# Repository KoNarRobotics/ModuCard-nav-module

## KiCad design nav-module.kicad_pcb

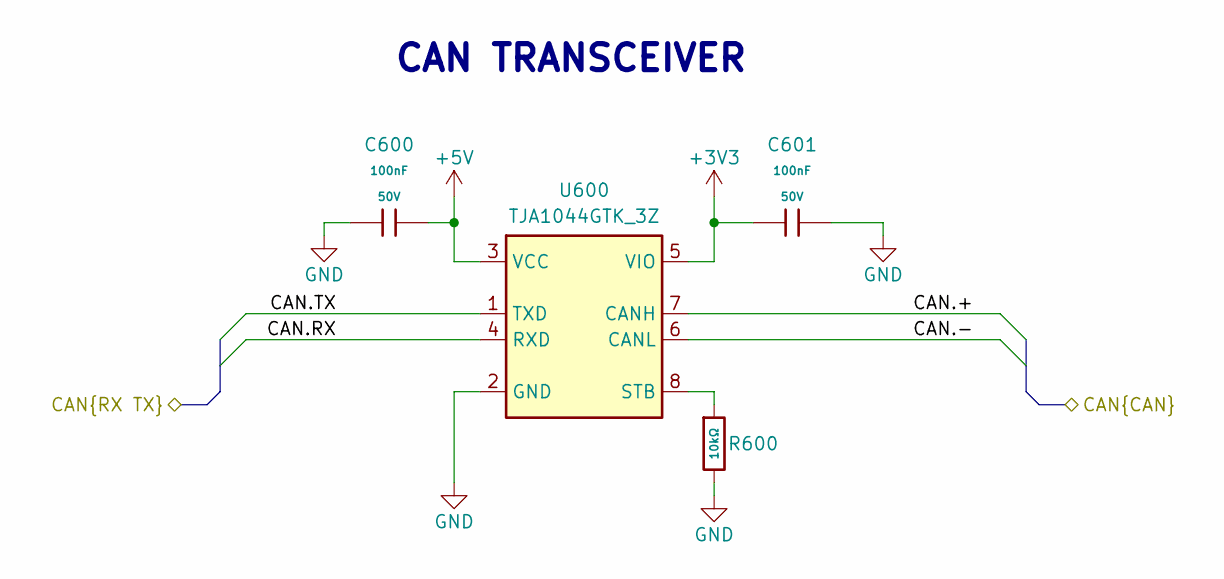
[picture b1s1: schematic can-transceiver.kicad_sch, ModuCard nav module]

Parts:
C600, C601: 100nF; C_0402; Voltage Rated 50V; Tolerance ±10%; Part CL05B104KB54PNC; LCSC C307331
R600: 10kΩ; R_0402; Overload Voltage (Max) 50V; Tolerance ±1%; Part 0402WGF1002TCE; LCSC C25744
U600: TJA1044GTK_3Z; HVSON-8-1EP_3x3mm_P0.65mm_EP1.6x2.4mm; Manufacturer_Part_Number TJA1044GTK/3Z

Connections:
+3V3: C601.1, U600.5 (VIO); also elsewhere on the board
+5V: C600.2, U600.3 (VCC); also elsewhere on the board
/Backplane/CAN2.+: U600.7 (CANH); also elsewhere on the board
/Backplane/CAN2.-: U600.6 (CANL); also elsewhere on the board
/CAN transceiver 2/CAN.RX: U600.4 (RXD); also elsewhere on the board
/CAN transceiver 2/CAN.TX: U600.1 (TXD); also elsewhere on the board
GND: C600.1, C601.2, R600.2, U600.2 (GND), U600.9 (EP); also elsewhere on the board
unnamed: R600.1, U600.8 (STB)

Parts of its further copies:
C500, C501: 100nF; C_0402; Voltage Rated 50V; Tolerance ±10%; Part CL05B104KB54PNC; LCSC C307331
R500: 10kΩ; R_0402; Overload Voltage (Max) 50V; Tolerance ±1%; Part 0402WGF1002TCE; LCSC C25744
U500: TJA1044GTK_3Z; HVSON-8-1EP_3x3mm_P0.65mm_EP1.6x2.4mm; Manufacturer_Part_Number TJA1044GTK/3Z

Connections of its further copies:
+3V3: C501.1, U500.5 (VIO); also elsewhere on the board
+5V: C500.2, U500.3 (VCC); also elsewhere on the board
/Backplane/CAN1.+: U500.7 (CANH); also elsewhere on the board
/Backplane/CAN1.-: U500.6 (CANL); also elsewhere on the board
/CAN transceiver 1/CAN.RX: U500.4 (RXD); also elsewhere on the board
/CAN transceiver 1/CAN.TX: U500.1 (TXD); also elsewhere on the board
GND: C500.1, C501.2, R500.2, U500.2 (GND), U500.9 (EP); also elsewhere on the board
unnamed: R500.1, U500.8 (STB)

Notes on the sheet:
CAN TRANSCEIVER

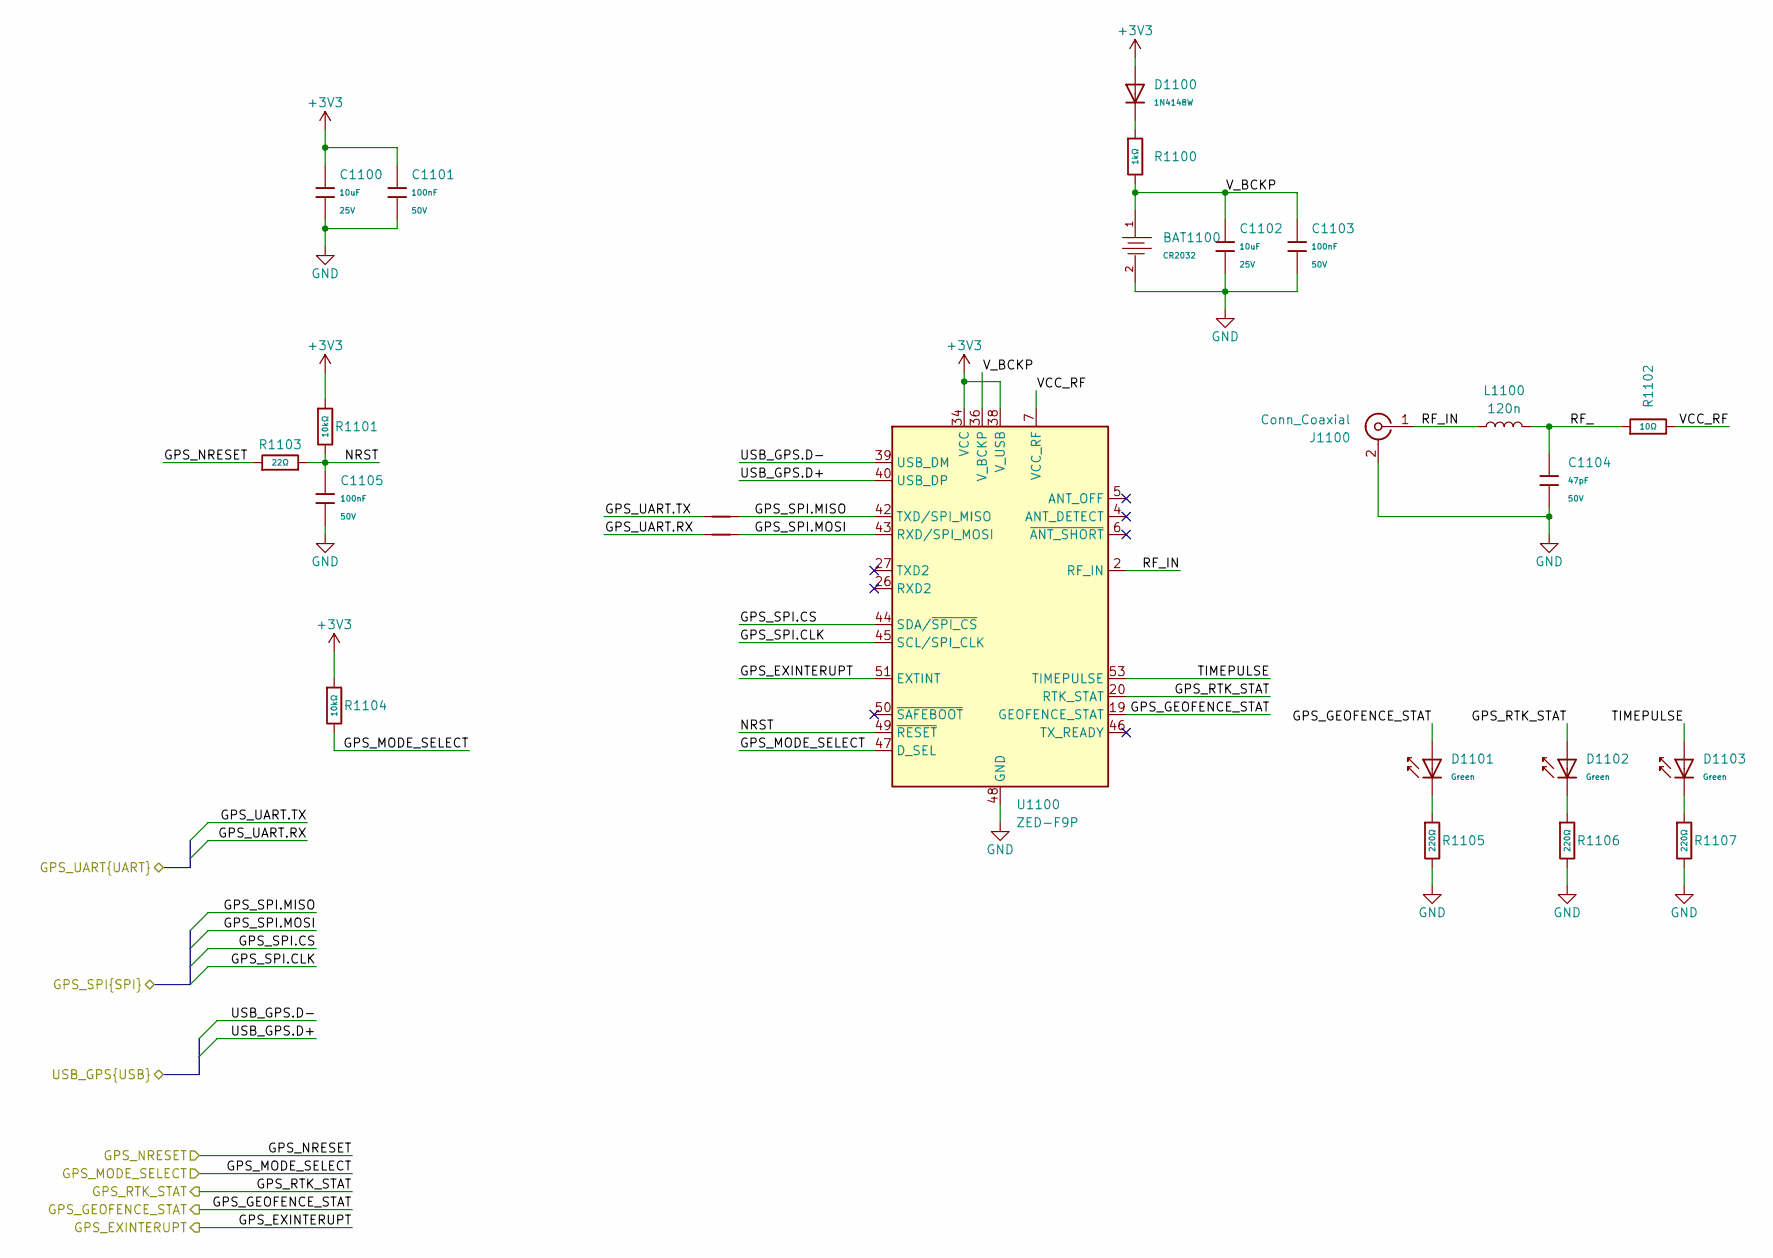
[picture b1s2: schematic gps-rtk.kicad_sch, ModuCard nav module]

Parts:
BAT1100: CR2032; BatteryHolder_Keystone_1060_1x2032; Part BS-07-A1BJ001; LCSC C2979167
C1100, C1102: 10uF; C_0603; Voltage Rated 25V; Tolerance ±20%; Part CL10A106MA8NRNC; LCSC C96446
C1101, C1103, C1105: 100nF; C_0402; Voltage Rated 50V; Tolerance ±10%; Part CL05B104KB54PNC; LCSC C307331
C1104: 47pF; C_0402; Voltage Rated 50V; Tolerance ±5%; Part 0402CG470J500NT; LCSC C1567
D1100: 1N4148W; D_SOD-123; Forward Voltage (Vf@If) 1V@50mA; Reverse Voltage (Vr) 75V; Part 1N4148W; LCSC C81598
D1101, D1102, D1103: Green; D_0603; Part 19-217/GHC-YR1S2/6T; LCSC C2986059
J1100: Conn_Coaxial; SMA_Amphenol_901-143_Horizontal
L1100: 120n; L_0402_1005Metric
NT1100, NT1101: NetTie_2; NetTie-2_SMD_Pad0.5mm
R1100: 1kΩ; R_0402; Overload Voltage (Max) 50V; Tolerance ±1%; Part 0402WGF1001TCE; LCSC C11702
R1101, R1104: 10kΩ; R_0402; Overload Voltage (Max) 50V; Tolerance ±1%; Part 0402WGF1002TCE; LCSC C25744
R1102: 10Ω; R_0402; Overload Voltage (Max) 50V; Tolerance ±1%; Part 0402WGF100JTCE; LCSC C25077
R1103: 22Ω; R_0402; Overload Voltage (Max) 50V; Tolerance ±1%; Part 0402WGF220JTCE; LCSC C25092
R1105, R1106, R1107: 220Ω; R_0402; Overload Voltage (Max) 50V; Tolerance ±1%; Part 0402WGF2200TCE; LCSC C25091
U1100: ZED-F9P; ublox_ZED

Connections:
+3V3: C1100.1, C1101.1, D1100.2, R1101.1, R1104.1, U1100.33 (VCC), U1100.34 (VCC), U1100.38 (V_USB); also elsewhere on the board
/GPS-RTK/GPS_EXINTERUPT: U1100.51 (EXTINT); also elsewhere on the board
/GPS-RTK/GPS_GEOFENCE_STAT: D1101.2, U1100.19 (GEOFENCE_STAT); also elsewhere on the board
/GPS-RTK/GPS_MODE_SELECT: R1104.2, U1100.47 (D_SEL); also elsewhere on the board
/GPS-RTK/GPS_NRESET: R1103.1; also elsewhere on the board
/GPS-RTK/GPS_RTK_STAT: D1102.2, U1100.20 (RTK_STAT); also elsewhere on the board
/GPS-RTK/GPS_SPI.CLK: U1100.45 (SCL/SPI_CLK); also elsewhere on the board
/GPS-RTK/GPS_SPI.CS: U1100.44 (SDA/~SPI_CS); also elsewhere on the board
/GPS-RTK/GPS_SPI.MISO: NT1100.2, U1100.42 (TXD/SPI_MISO); also elsewhere on the board
/GPS-RTK/GPS_SPI.MOSI: NT1101.2, U1100.43 (RXD/SPI_MOSI); also elsewhere on the board
/GPS-RTK/GPS_UART.RX: NT1101.1; also elsewhere on the board
/GPS-RTK/GPS_UART.TX: NT1100.1; also elsewhere on the board
/GPS-RTK/NRST: C1105.1, R1101.2, R1103.2, U1100.49 (~RESET)
/GPS-RTK/RF_: C1104.2, L1100.2, R1102.1
/GPS-RTK/RF_IN: J1100.1 (In), L1100.1, U1100.2 (RF_IN)
/GPS-RTK/TIMEPULSE: D1103.2, U1100.53 (TIMEPULSE)
/GPS-RTK/USB_GPS.D+: U1100.40 (USB_DP); also elsewhere on the board
/GPS-RTK/USB_GPS.D-: U1100.39 (USB_DM); also elsewhere on the board
/GPS-RTK/VCC_RF: R1102.2, U1100.7 (VCC_RF)
/GPS-RTK/V_BCKP: BAT1100.1, C1102.1, C1103.1, R1100.2, U1100.36 (V_BCKP)
GND: BAT1100.2, C1100.2, C1101.2, C1102.2, C1103.2, C1104.1, C1105.2, J1100.2 (Ext), R1105.2, R1106.2, R1107.2, U1100.1 (GND), U1100.3 (GND), U1100.12 (GND), U1100.14 (GND), U1100.32 (GND), U1100.37 (GND), U1100.41 (GND), U1100.48 (GND), U1100.55 (GND); also elsewhere on the board
unnamed: D1100.1, R1100.1
unnamed: D1101.1, R1105.1
unnamed: D1102.1, R1106.1
unnamed: D1103.1, R1107.1

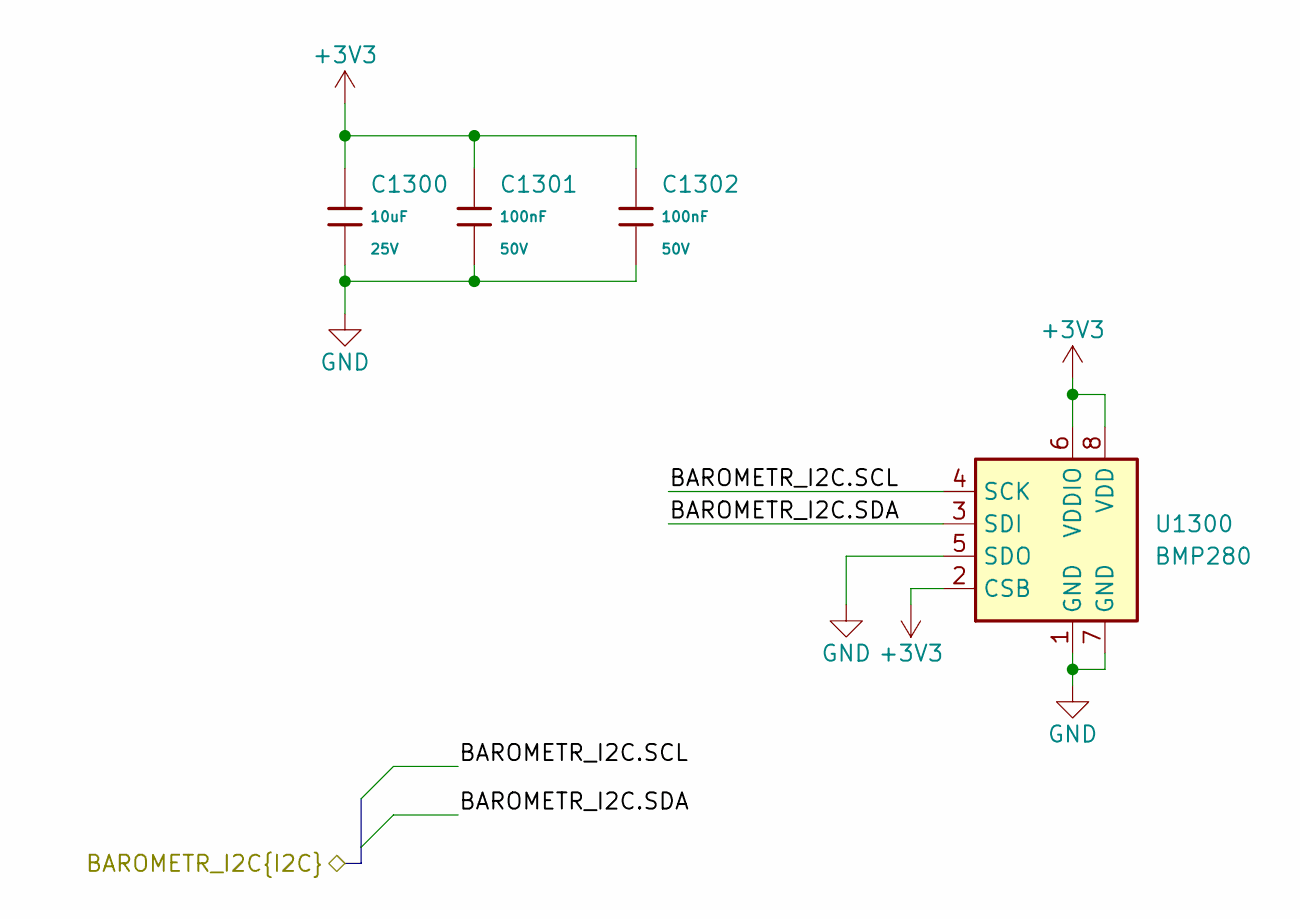
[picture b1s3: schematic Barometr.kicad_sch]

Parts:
C1300: 10uF; C_0603; Voltage Rated 25V; Tolerance ±20%; Part CL10A106MA8NRNC; LCSC C96446
C1301, C1302: 100nF; C_0402; Voltage Rated 50V; Tolerance ±10%; Part CL05B104KB54PNC; LCSC C307331
U1300: BMP280; Bosch_LGA-8_2x2.5mm_P0.65mm_ClockwisePinNumbering

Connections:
+3V3: C1300.1, C1301.1, C1302.1, U1300.2 (CSB), U1300.6 (VDDIO), U1300.8 (VDD); also elsewhere on the board
/Barometr/BAROMETR_I2C.SCL: U1300.4 (SCK); also elsewhere on the board
/Barometr/BAROMETR_I2C.SDA: U1300.3 (SDI); also elsewhere on the board
GND: C1300.2, C1301.2, C1302.2, U1300.1 (GND), U1300.5 (SDO), U1300.7 (GND); also elsewhere on the board

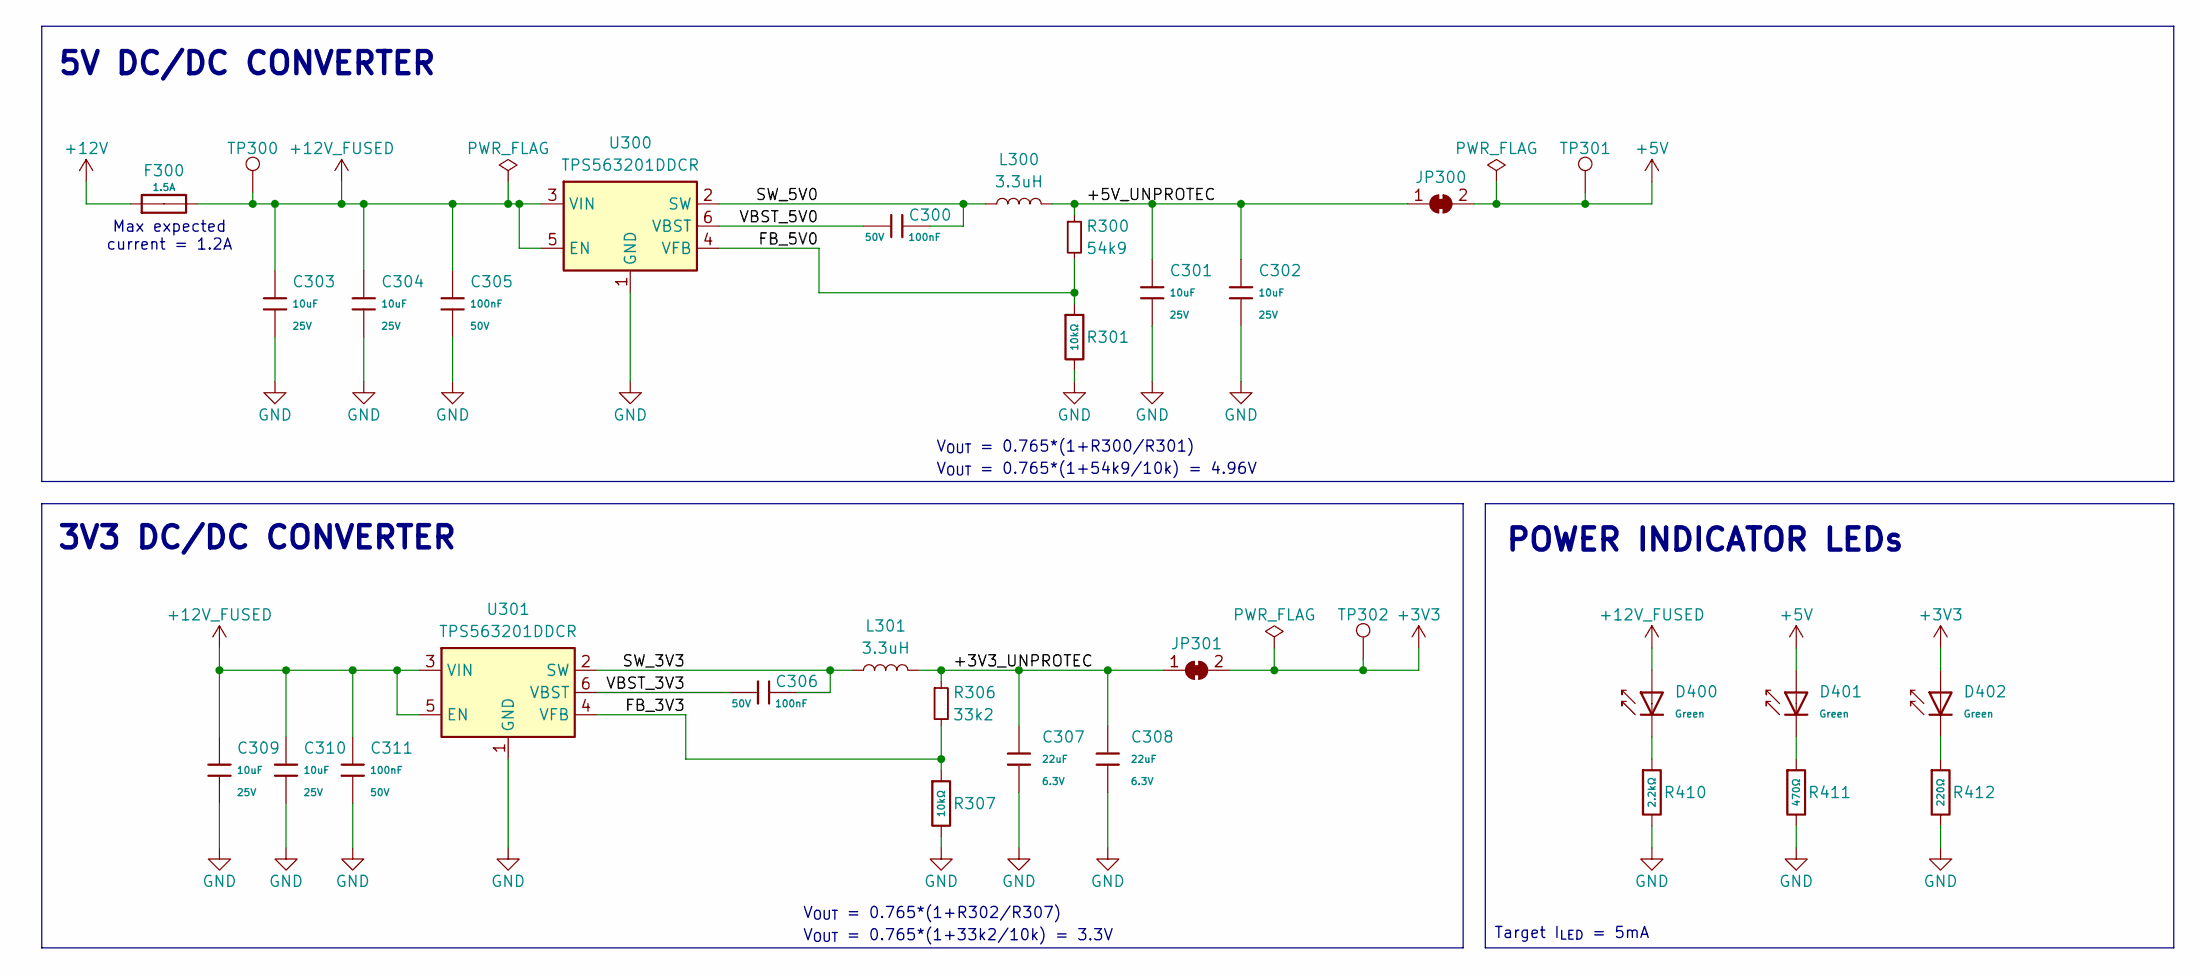
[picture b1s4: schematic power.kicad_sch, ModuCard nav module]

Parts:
C300, C305, C306, C311: 100nF; C_0402; Voltage Rated 50V; Tolerance ±10%; Part CL05B104KB54PNC; LCSC C307331
C301, C302, C303, C304, C309, C310: 10uF; C_0603; Voltage Rated 25V; Tolerance ±20%; Part CL10A106MA8NRNC; LCSC C96446
C307, C308: 22uF; C_0603; Voltage Rated 6.3V; Tolerance ±20%; Part CL10A226MQ8NRNC; LCSC C59461
D400, D401, D402: Green; D_0603; Part 19-217/GHC-YR1S2/6T; LCSC C2986059
F300: 1.5A; F_0603; Part F06F1.5; LCSC C2924957
JP300, JP301: Test Buck Vout; SolderJumper-2_P1.3mm_Open_TrianglePad1.0x1.5mm
L300, L301: 3.3uH; L_Changjiang_FXL0420
R300: 54k9; R_0402
R301, R307: 10kΩ; R_0402; Overload Voltage (Max) 50V; Tolerance ±1%; Part 0402WGF1002TCE; LCSC C25744
R306: 33k2; R_0402
R410: 2.2kΩ; R_0402; Overload Voltage (Max) 50V; Tolerance ±1%; Part 0402WGF2201TCE; LCSC C25879
R411: 470Ω; R_0402; Overload Voltage (Max) 50V; Tolerance ±1%; Part 0402WGF4700TCE; LCSC C25117
R412: 220Ω; R_0402; Overload Voltage (Max) 50V; Tolerance ±1%; Part 0402WGF2200TCE; LCSC C25091
TP300, TP301, TP302: TestPoint; TestPoint_Pad_D1.0mm
U300, U301: TPS563201DDCR; SOT-23-6

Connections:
+3V3: D402.2, JP301.2 (B), TP302.1; also elsewhere on the board
+5V: D401.2, JP300.2 (B), TP301.1; also elsewhere on the board
+12V: F300.1; also elsewhere on the board
+12V_FUSED: C303.1, C304.1, C305.2, C309.1, C310.1, C311.2, D400.2, F300.2, TP300.1, U300.3 (VIN), U300.5 (EN), U301.3 (VIN), U301.5 (EN)
/Power/+3V3_UNPROTEC: C307.1, C308.1, JP301.1 (A), L301.2, R306.1
/Power/+5V_UNPROTEC: C301.1, C302.1, JP300.1 (A), L300.2, R300.1
/Power/FB_3V3: R306.2, R307.1, U301.4 (VFB)
/Power/FB_5V0: R300.2, R301.1, U300.4 (VFB)
/Power/SW_3V3: C306.2, L301.1, U301.2 (SW)
/Power/SW_5V0: C300.2, L300.1, U300.2 (SW)
/Power/VBST_3V3: C306.1, U301.6 (VBST)
/Power/VBST_5V0: C300.1, U300.6 (VBST)
GND: C301.2, C302.2, C303.2, C304.2, C305.1, C307.2, C308.2, C309.2, C310.2, C311.1, R301.2, R307.2, R410.2, R411.2, R412.2, U300.1 (GND), U301.1 (GND); also elsewhere on the board
unnamed: D400.1, R410.1
unnamed: D401.1, R411.1
unnamed: D402.1, R412.1

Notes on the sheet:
V_{OUT} = 0.765*(1+33k2/10k) = 3.3V
Max expected current = 1.2A
V_{OUT} = 0.765*(1+R302/R307)
Target I_{LED} = 5mA
V_{OUT} = 0.765*(1+R300/R301)
5V DC/DC CONVERTER
V_{OUT} = 0.765*(1+54k9/10k) = 4.96V
POWER INDICATOR LEDs
3V3 DC/DC CONVERTER

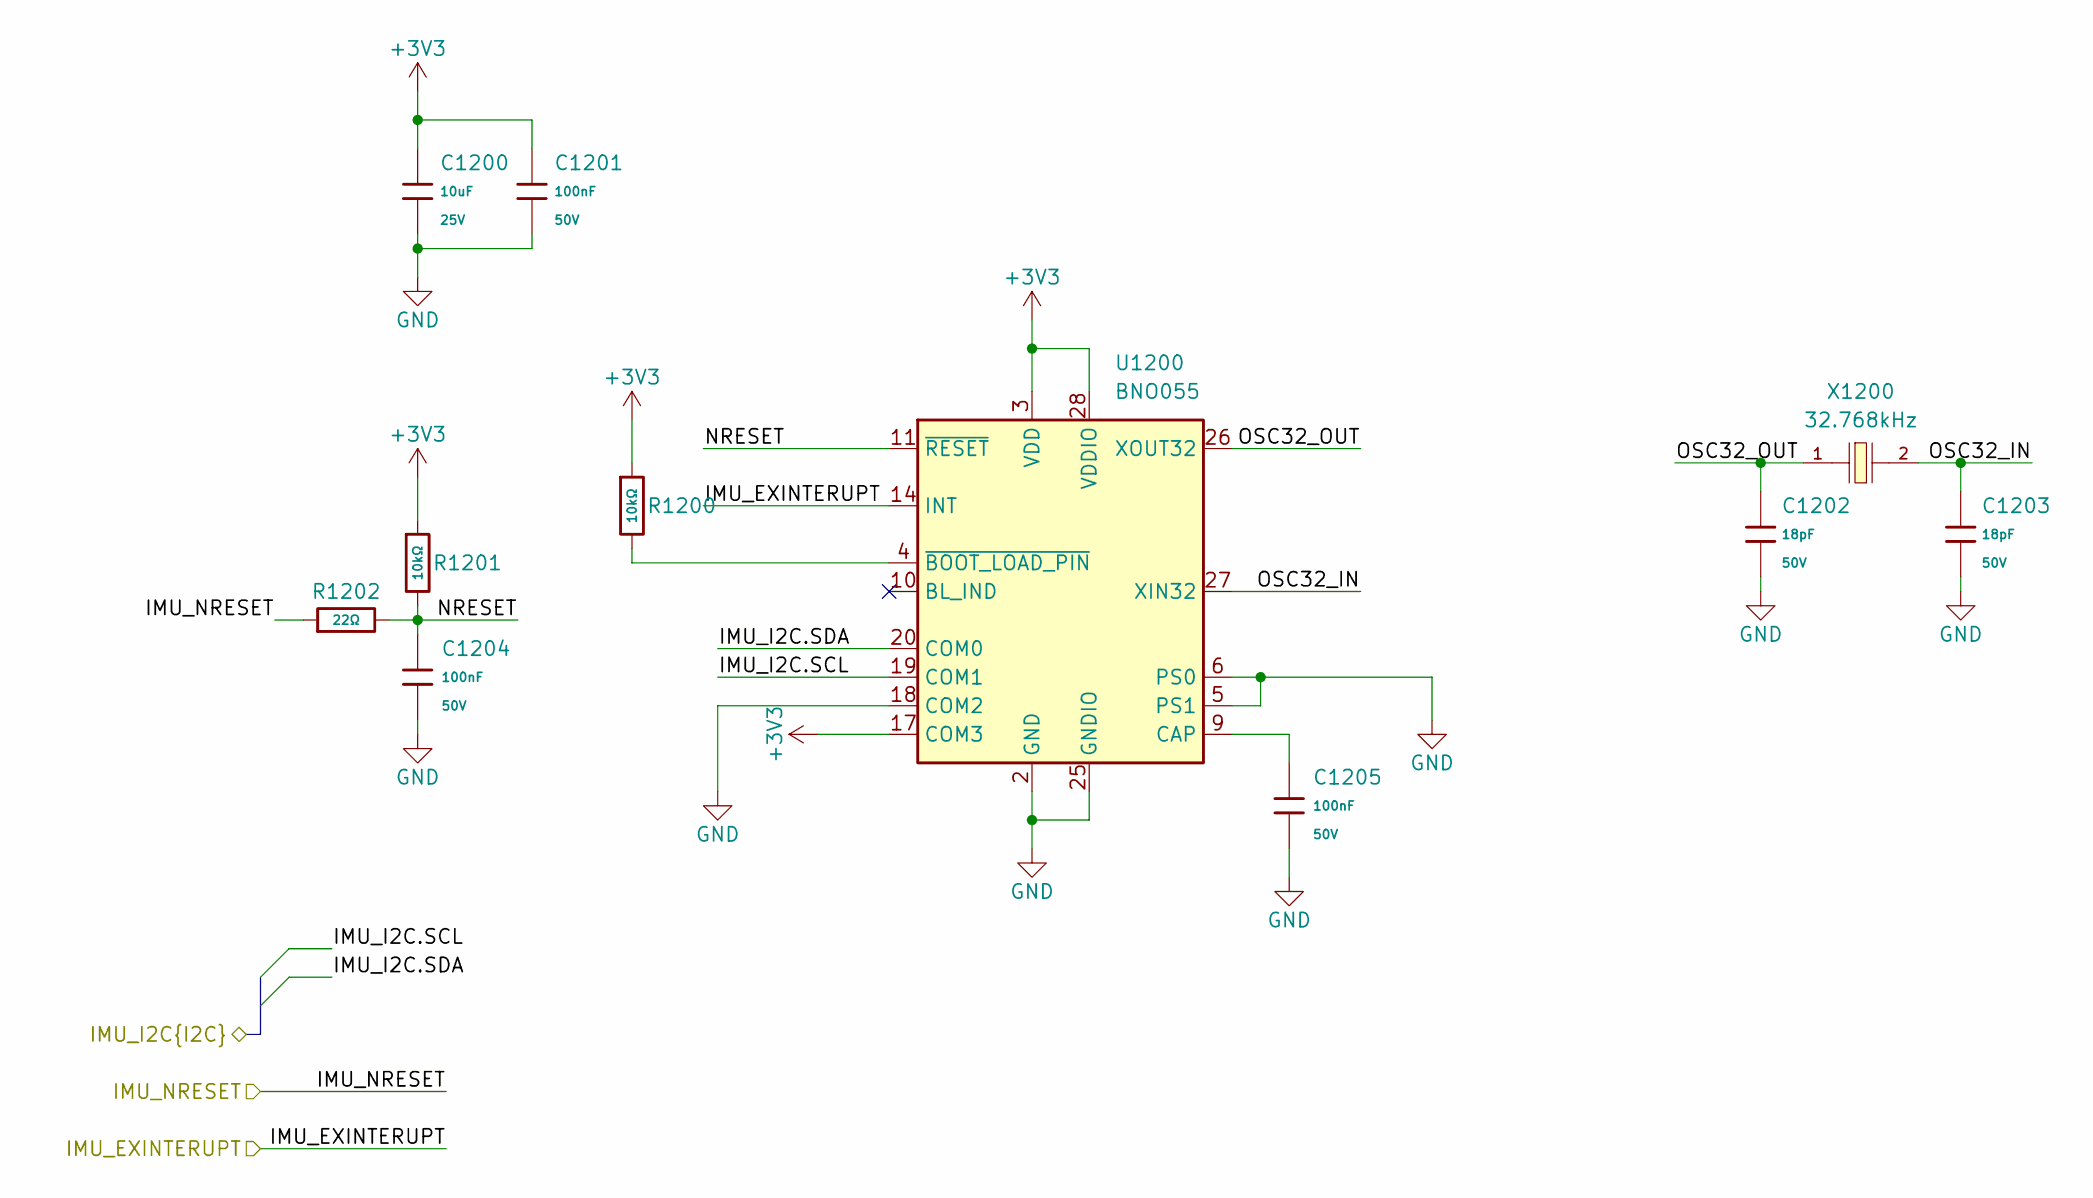
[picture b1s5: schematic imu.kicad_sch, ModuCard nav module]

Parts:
C1200: 10uF; C_0603; Voltage Rated 25V; Tolerance ±20%; Part CL10A106MA8NRNC; LCSC C96446
C1201, C1204, C1205: 100nF; C_0402; Voltage Rated 50V; Tolerance ±10%; Part CL05B104KB54PNC; LCSC C307331
C1202, C1203: 18pF; C_0402; Voltage Rated 50V; Tolerance ±5%; Part 0402CG180J500NT; LCSC C1549
R1200, R1201: 10kΩ; R_0402; Overload Voltage (Max) 50V; Tolerance ±1%; Part 0402WGF1002TCE; LCSC C25744
R1202: 22Ω; R_0402; Overload Voltage (Max) 50V; Tolerance ±1%; Part 0402WGF220JTCE; LCSC C25092
U1200: BNO055; LGA-28_5.2x3.8mm_P0.5mm
X1200: Q13FC1350000400; FC-135R_L3.2-W1.5; Frequency Tolerance ±20ppm; Part Q13FC13500004; LCSC C32346

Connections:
+3V3: C1200.1, C1201.1, R1200.1, R1201.1, U1200.3 (VDD), U1200.17 (COM3), U1200.28 (VDDIO); also elsewhere on the board
/Barometr/BAROMETR_I2C.SCL: U1200.19 (COM1); also elsewhere on the board
/Barometr/BAROMETR_I2C.SDA: U1200.20 (COM0); also elsewhere on the board
/IMU/IMU_EXINTERUPT: U1200.14 (INT); also elsewhere on the board
/IMU/IMU_NRESET: R1202.1; also elsewhere on the board
/IMU/NRESET: C1204.1, R1201.2, R1202.2, U1200.11 (~RESET)
/IMU/OSC32_IN: C1203.1, U1200.27 (XIN32), X1200.2
/IMU/OSC32_OUT: C1202.1, U1200.26 (XOUT32), X1200.1
GND: C1200.2, C1201.2, C1202.2, C1203.2, C1204.2, C1205.2, U1200.2 (GND), U1200.5 (PS1), U1200.6 (PS0), U1200.18 (COM2), U1200.25 (GNDIO); also elsewhere on the board
unnamed: C1205.1, U1200.9 (CAP)
unnamed: R1200.2, U1200.4 (~BOOT_LOAD_PIN)

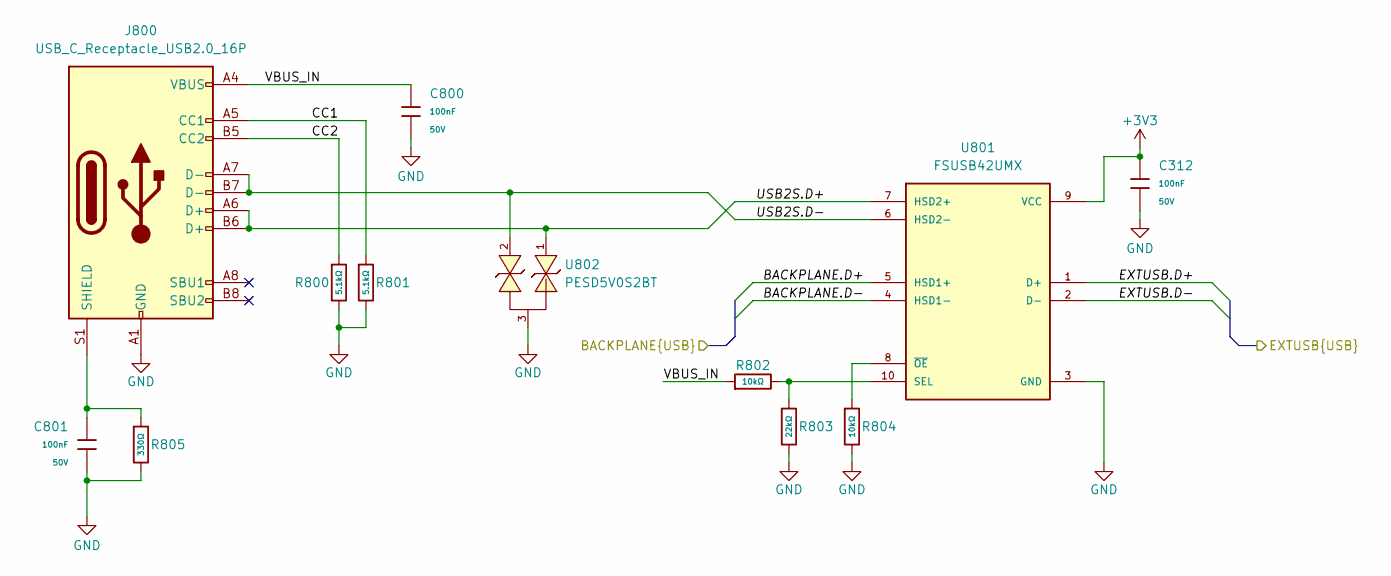
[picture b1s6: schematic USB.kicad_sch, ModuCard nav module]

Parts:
C312, C800, C801: 100nF; C_0402; Voltage Rated 50V; Tolerance ±10%; Part CL05B104KB54PNC; LCSC C307331
J800: USB_C_Receptacle_USB2.0_16P; USB_C_Receptacle_GCT_USB4105-xx-A_16P_TopMnt_Horizontal
R800, R801: 5.1kΩ; R_0402; Overload Voltage (Max) 50V; Tolerance ±1%; Part 0402WGF5101TCE; LCSC C25905
R802, R804: 10kΩ; R_0402; Overload Voltage (Max) 50V; Tolerance ±1%; Part 0402WGF1002TCE; LCSC C25744
R803: 22kΩ; R_0402; Overload Voltage (Max) 50V; Tolerance ±1%; Part 0402WGF2202TCE; LCSC C25768
R805: 330Ω; R_0402; Overload Voltage (Max) 50V; Tolerance ±1%; Part 0402WGF3300TCE; LCSC C25104
U801: FSUSB42UMX; UQFN-10_1.4x1.8mm_P0.4mm; PARTREV 1.25
U802: PESD5V0S2BT; SOT-23

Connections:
+3V3: C312.1, U801.9 (VCC); also elsewhere on the board
/Backplane/BACKPLANE.D+: U801.5 (HSD1+); also elsewhere on the board
/Backplane/BACKPLANE.D-: U801.4 (HSD1-); also elsewhere on the board
/USB-hub/USBIN1.D+: U801.1 (D+); also elsewhere on the board
/USB-hub/USBIN1.D-: U801.2 (D-); also elsewhere on the board
/USB/CC1: J800.A5 (CC1), R801.1
/USB/CC2: J800.B5 (CC2), R800.1
/USB/USB2S.D+: J800.A6 (D+), J800.B6 (D+), U801.7 (HSD2+), U802.1
/USB/USB2S.D-: J800.A7 (D-), J800.B7 (D-), U801.6 (HSD2-), U802.2
/USB/VBUS_IN: C800.1, J800.A4 (VBUS), J800.A9 (VBUS), J800.B4 (VBUS), J800.B9 (VBUS), R802.1
GND: C312.2, C800.2, C801.2, J800.A1 (GND), J800.A12 (GND), J800.B1 (GND), J800.B12 (GND), R800.2, R801.2, R803.2, R804.2, R805.2, U801.3 (GND), U802.3; also elsewhere on the board
unnamed: C801.1, J800.S1 (SHIELD), R805.1
unnamed: R802.2, R803.1, U801.10 (SEL)
unnamed: R804.1, U801.8 (~OE)

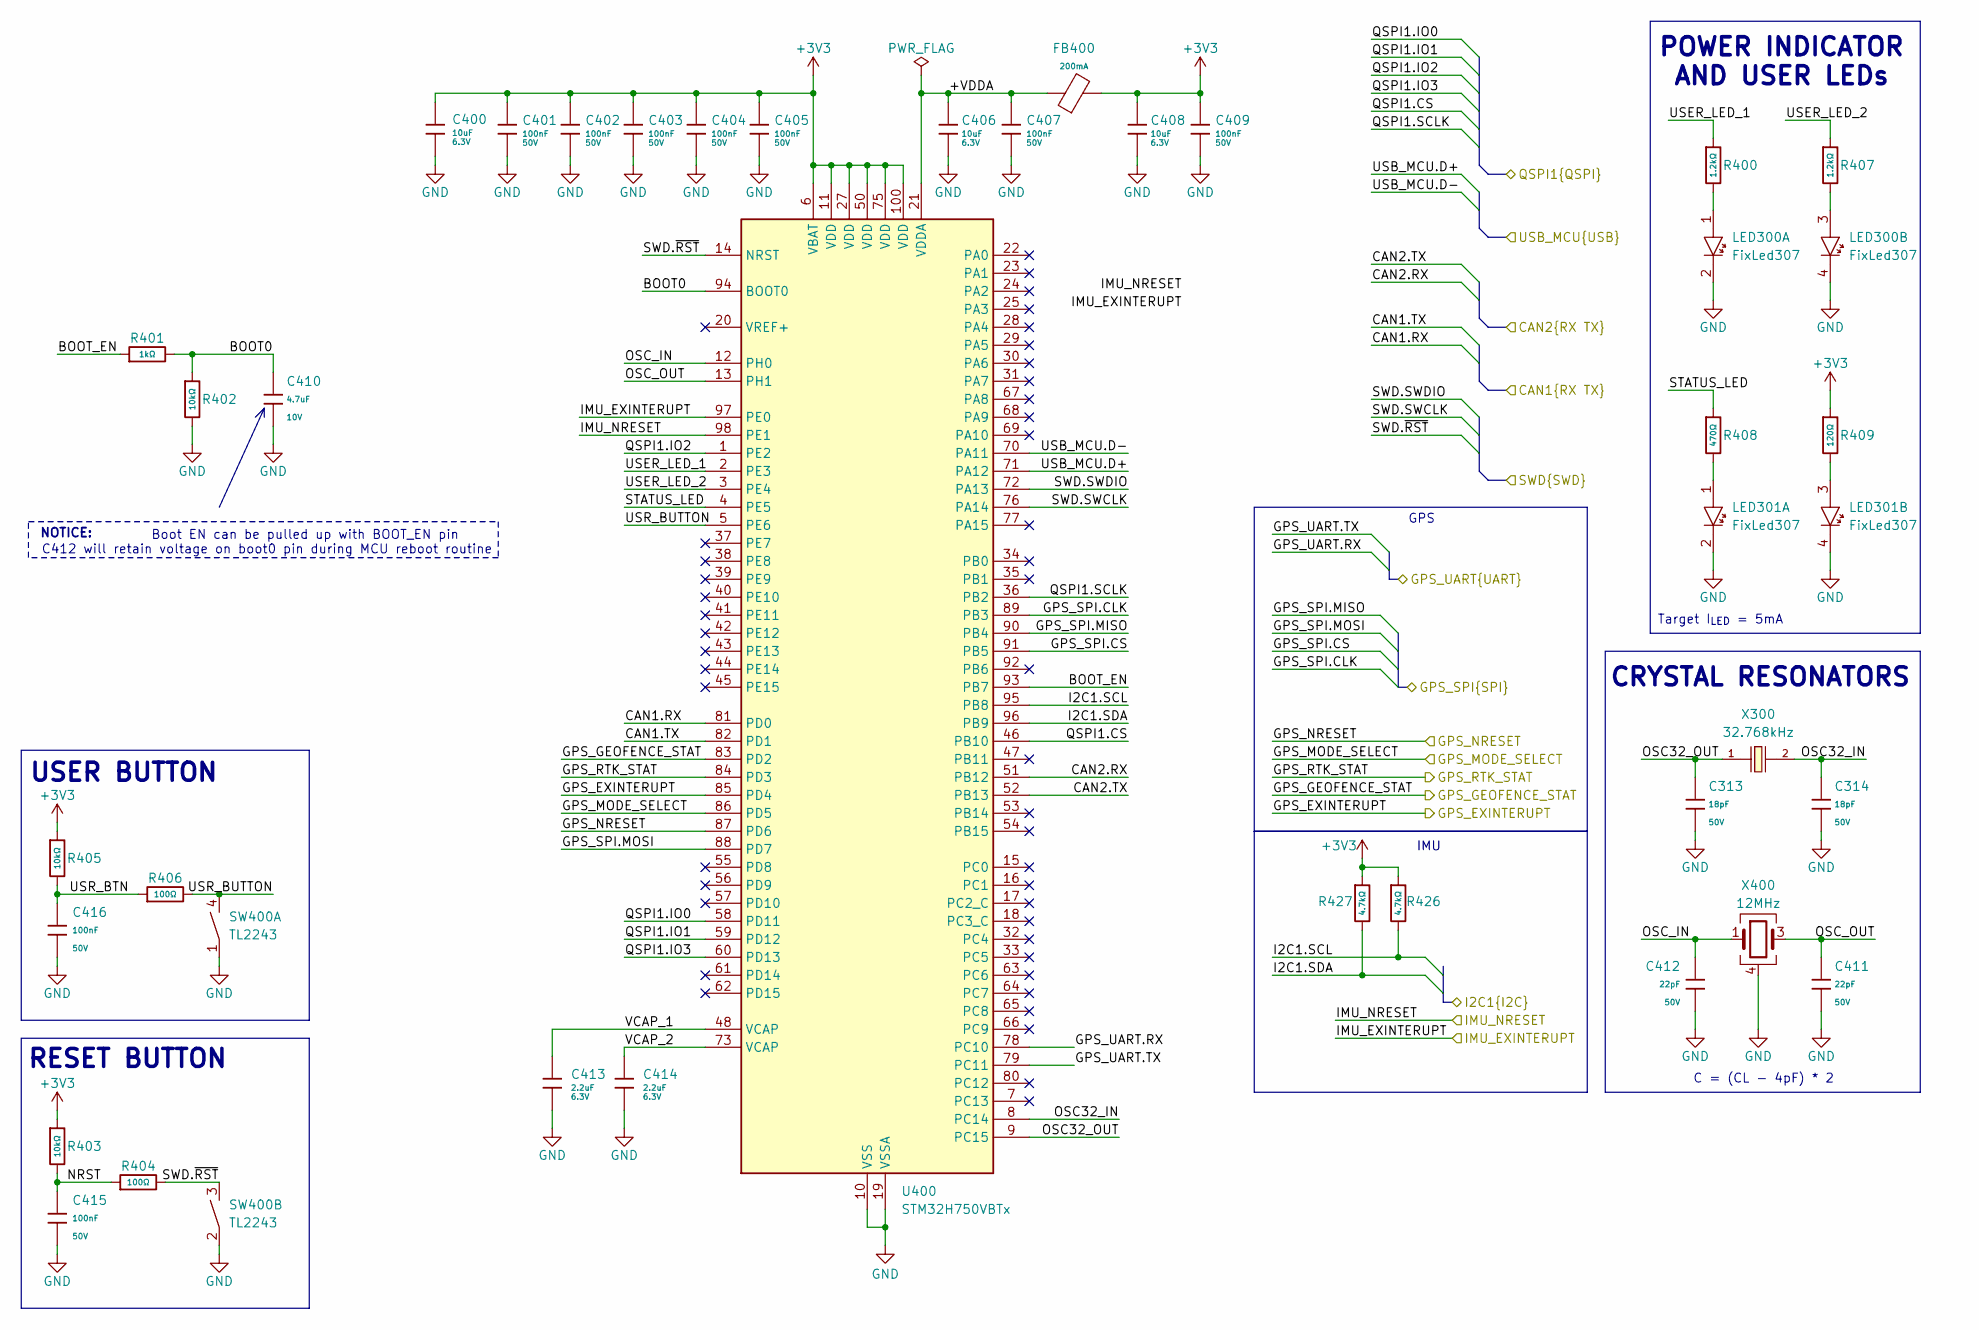
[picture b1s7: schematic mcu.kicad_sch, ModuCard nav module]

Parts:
C313, C314: 18pF; C_0402; Voltage Rated 50V; Tolerance ±5%; Part 0402CG180J500NT; LCSC C1549
C400, C406, C408: 10uF; C_0402; Voltage Rated 6.3V; Tolerance ±20%; Part CL05A106MQ5NUNC; LCSC C15525
C401, C402, C403, C404, C405, C407, C409, C415, C416: 100nF; C_0402; Voltage Rated 50V; Tolerance ±10%; Part CL05B104KB54PNC; LCSC C307331
C410: 4.7uF; C_0402; Voltage Rated 10V; Tolerance ±20%; Part CL05A475MP5NRNC; LCSC C23733
C411, C412: 22pF; C_0402; Voltage Rated 50V; Tolerance ±5%; Part 0402CG220J500NT; LCSC C1555
C413, C414: 2.2uF; C_0402; Voltage Rated 6.3V; Tolerance ±20%; Part CL05A225MQ5NSNC; LCSC C12530
FB400: FB_0603; Current Rating 200mA; Tolerance ±25%; Part GZ1608D601TF; LCSC C1002
LED300, LED301: FixLed307
R400, R407: 1.2kΩ; R_0402; Overload Voltage (Max) 50V; Tolerance ±1%; Part 0402WGF1201TCE; LCSC C25862
R401: 1kΩ; R_0402; Overload Voltage (Max) 50V; Tolerance ±1%; Part 0402WGF1001TCE; LCSC C11702
R402, R403, R405: 10kΩ; R_0402; Overload Voltage (Max) 50V; Tolerance ±1%; Part 0402WGF1002TCE; LCSC C25744
R404, R406: 100Ω; R_0402; Overload Voltage (Max) 50V; Tolerance ±1%; Part 0402WGF1000TCE; LCSC C25076
R408: 470Ω; R_0402; Overload Voltage (Max) 50V; Tolerance ±1%; Part 0402WGF4700TCE; LCSC C25117
R409: 120Ω; R_0402; Overload Voltage (Max) 50V; Tolerance ±1%; Part 0402WGF1200TCE; LCSC C25079
R426, R427: 4.7kΩ; R_0402; Overload Voltage (Max) 50V; Tolerance ±1%; Part 0402WGF4701TCE; LCSC C25900
SW400: TL2243
U400: STM32H750VBTx; LQFP-100_14x14mm_P0.5mm
X300: Q13FC1350000400; FC-135R_L3.2-W1.5; Frequency Tolerance ±20ppm; Part Q13FC13500004; LCSC C32346
X400: X322512MSB4SI; CRYSTAL-SMD_4P-L3.2-W2.5-BL; Frequency Tolerance ±10ppm; Part X322512MSB4SI; LCSC C9002

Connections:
+3V3: C400.1, C401.1, C402.1, C403.1, C404.1, C405.1, C408.1, C409.1, FB400.2, R403.1, R405.1, R409.1, R426.1, R427.1, U400.6 (VBAT), U400.11 (VDD), U400.27 (VDD), U400.50 (VDD), U400.75 (VDD), U400.100 (VDD); also elsewhere on the board
/Barometr/BAROMETR_I2C.SCL: R426.2, U400.95 (PB8); also elsewhere on the board
/Barometr/BAROMETR_I2C.SDA: R427.2, U400.96 (PB9); also elsewhere on the board
/CAN transceiver 1/CAN.RX: U400.81 (PD0); also elsewhere on the board
/CAN transceiver 1/CAN.TX: U400.82 (PD1); also elsewhere on the board
/CAN transceiver 2/CAN.RX: U400.51 (PB12); also elsewhere on the board
/CAN transceiver 2/CAN.TX: U400.52 (PB13); also elsewhere on the board
/GPS-RTK/GPS_EXINTERUPT: U400.85 (PD4); also elsewhere on the board
/GPS-RTK/GPS_GEOFENCE_STAT: U400.83 (PD2); also elsewhere on the board
/GPS-RTK/GPS_MODE_SELECT: U400.86 (PD5); also elsewhere on the board
/GPS-RTK/GPS_NRESET: U400.87 (PD6); also elsewhere on the board
/GPS-RTK/GPS_RTK_STAT: U400.84 (PD3); also elsewhere on the board
/GPS-RTK/GPS_SPI.CLK: U400.89 (PB3); also elsewhere on the board
/GPS-RTK/GPS_SPI.CS: U400.91 (PB5); also elsewhere on the board
/GPS-RTK/GPS_SPI.MISO: U400.90 (PB4); also elsewhere on the board
/GPS-RTK/GPS_SPI.MOSI: U400.88 (PD7); also elsewhere on the board
/GPS-RTK/GPS_UART.RX: U400.78 (PC10); also elsewhere on the board
/GPS-RTK/GPS_UART.TX: U400.79 (PC11); also elsewhere on the board
/IMU/IMU_EXINTERUPT: U400.97 (PE0); also elsewhere on the board
/IMU/IMU_NRESET: U400.98 (PE1); also elsewhere on the board
/MCU/+VDDA: C406.1, C407.1, FB400.1, U400.21 (VDDA)
/MCU/BOOT0: C410.1, R401.2, R402.1, U400.94 (BOOT0)
/MCU/BOOT_EN: R401.1, U400.93 (PB7)
/MCU/NRST: C415.1, R403.2, R404.1
/MCU/OSC32_IN: C314.1, U400.8 (PC14), X300.2
/MCU/OSC32_OUT: C313.1, U400.9 (PC15), X300.1
/MCU/OSC_IN: C412.1, U400.12 (PH0), X400.1
/MCU/OSC_OUT: C411.1, U400.13 (PH1), X400.3
/MCU/QSPI1.CS: U400.46 (PB10); also elsewhere on the board
/MCU/QSPI1.IO0: U400.58 (PD11); also elsewhere on the board
/MCU/QSPI1.IO1: U400.59 (PD12); also elsewhere on the board
/MCU/QSPI1.IO2: U400.1 (PE2); also elsewhere on the board
/MCU/QSPI1.IO3: U400.60 (PD13); also elsewhere on the board
/MCU/QSPI1.SCLK: U400.36 (PB2); also elsewhere on the board
/MCU/STATUS_LED: R408.1, U400.4 (PE5)
/MCU/SWD.SWCLK: U400.76 (PA14); also elsewhere on the board
/MCU/SWD.SWDIO: U400.72 (PA13); also elsewhere on the board
/MCU/SWD.~RST: R404.2, SW400.3, U400.14 (NRST); also elsewhere on the board
/MCU/USB_MCU.D+: U400.71 (PA12); also elsewhere on the board
/MCU/USB_MCU.D-: U400.70 (PA11); also elsewhere on the board
/MCU/USER_LED_1: R400.1, U400.2 (PE3)
/MCU/USER_LED_2: R407.1, U400.3 (PE4)
/MCU/USR_BTN: C416.1, R405.2, R406.1
/MCU/USR_BUTTON: R406.2, SW400.4, U400.5 (PE6)
/MCU/VCAP_1: C413.1, U400.48 (VCAP)
/MCU/VCAP_2: C414.1, U400.73 (VCAP)
GND: C313.2, C314.2, C400.2, C401.2, C402.2, C403.2, C404.2, C405.2, C406.2, C407.2, C408.2, C409.2, C410.2, C411.2, C412.2, C413.2, C414.2, C415.2, C416.2, LED300.2, LED300.4, LED301.2, LED301.4, R402.2, SW400.1, SW400.2, U400.10 (VSS), U400.19 (VSSA), U400.26 (VSS), U400.49 (VSS), U400.74 (VSS), U400.99 (VSS), X400.2, X400.4; also elsewhere on the board
unnamed: LED300.1, R400.2
unnamed: LED300.3, R407.2
unnamed: LED301.1, R408.2
unnamed: LED301.3, R409.2

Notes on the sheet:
Boot EN can be pulled up with BOOT_EN pin C412 will retain voltage on boot0 pin during MCU reboot routine
GPS
RESET BUTTON
C = (CL - 4pF) * 2
CRYSTAL RESONATORS
POWER INDICATOR AND USER LEDs
NOTICE:
Target I_{LED} = 5mA
USER BUTTON
IMU
